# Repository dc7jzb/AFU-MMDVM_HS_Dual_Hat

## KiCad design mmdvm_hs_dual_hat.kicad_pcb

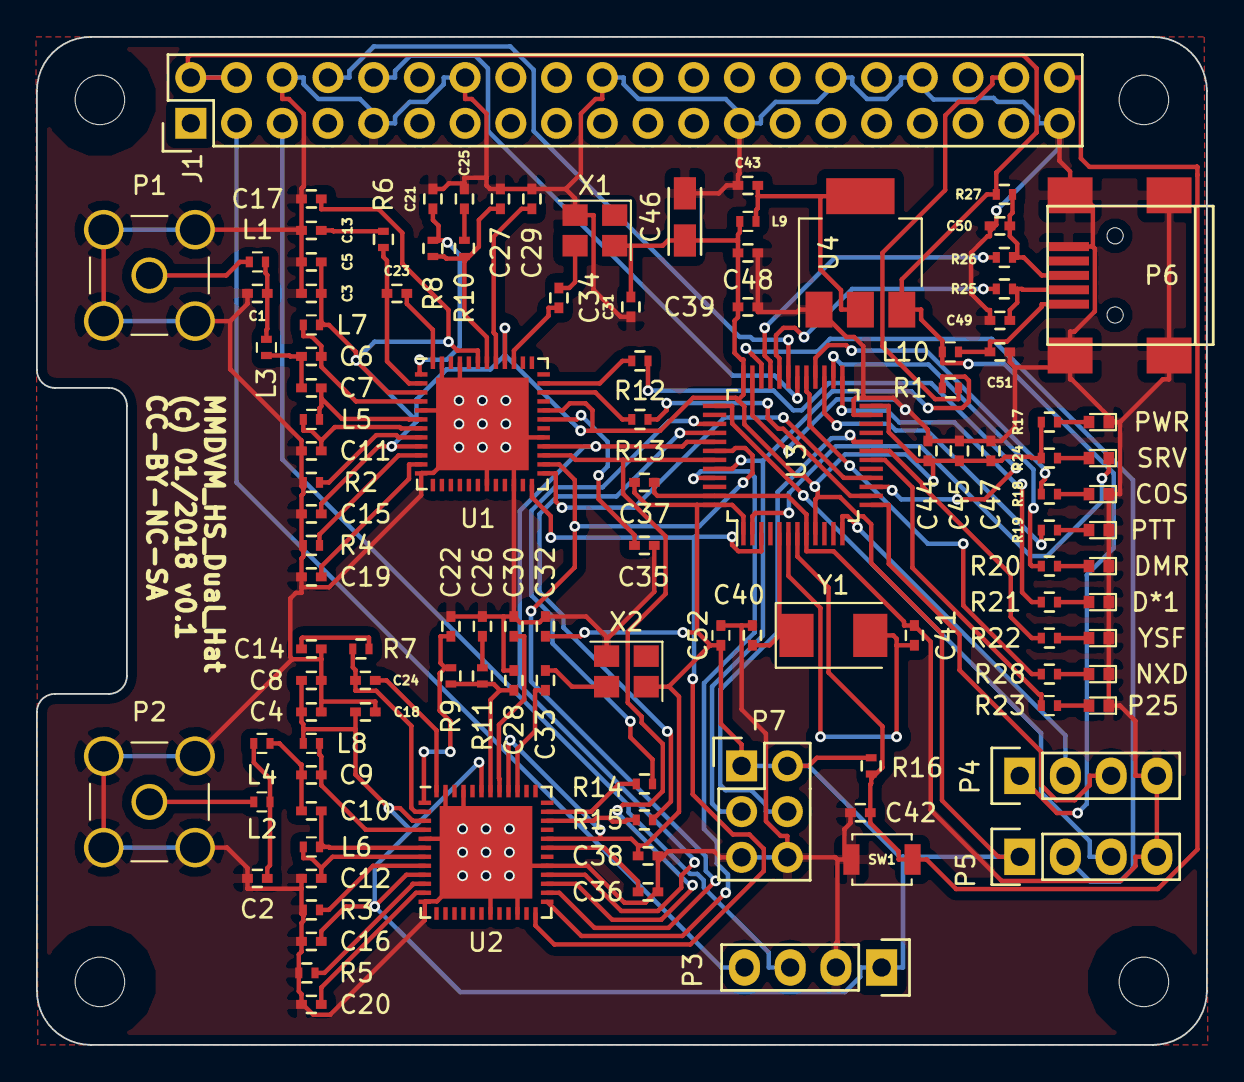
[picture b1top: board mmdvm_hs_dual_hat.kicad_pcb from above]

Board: 2 copper layers, 65.0 x 56.0 mm, 119 parts (0 on the bottom side), 92 nets.

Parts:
C1, C2, C11, C12: 6p8; C_0402
C3, C4, C15, C16, C17, C18, C31, C32, C37, C38, C39, C51, C52: 10n; C_0402
C5, C8: 220p; C_0402
C6, C9: 10p; C_0402
C7, C10: 4p7; C_0402
C13, C14, C19, C20, C29, C30, C35, C36, C42, C43, C44, C45, C47: 100n; C_0402
C21, C22: 470p; C_0402
C23, C24: 22n; C_0402
C25, C26: 15n; C_0402
C27, C28: 1n; C_0402
C33, C34: 22p; C_0402
C40, C41: 20p; C_0402
C46: 10u/10V; TantalC_SizeA_EIA-3216_Reflow
C48: 10u; C_0402
C49, C50: 47p; C_0402
COS: yellow; LED_0402
D*1: green; LED_0402
DMR: yellow; LED_0402
J1: RPi_GPIO; Pin_Header_Straight_2x20
L1, L2: 22n; L_0402
L3, L4: 20n; L_0402
L5, L6: 27n; L_0402
L7, L8: 13n; L_0402
L9: 10u; L_0402
L10: 100MHz; L_0402
NXD: blue; LED_0402
P1, P2: SMA; SMA_THT_Jack_Straight
P3: I2C; Pin_Header_Straight_1x04
P4: DISPLAY; Pin_Header_Straight_1x04
P5: STLINK; Pin_Header_Straight_1x04
P6: USB_OTG; USB_Mini-B
P7: CONN_02X03; Pin_Header_Straight_2x03
P25: red; LED_0402
PTT: red; LED_0402
PWR: green; LED_0402
R1, R16: 10k; R_0402
R2, R3: 1k1; R_0402
R4, R5: 3k8; R_0402
R6, R7: 3r9; R_0402
R8, R9: 560; R_0402
R10, R11: 270; R_0402
R12, R13, R14, R15, R17, R18, R19, R20, R21, R22, R23, R24, R28: 1k; R_0402
R25, R26: 27R; R_0402
R27: 1k5; R_0402
SRV: red; LED_0402
SW1: DNI; SW_SPST_B3U-1000P
U1, U2: ADF7021; QFN-48-1EP_7x7mm_Pitch0.5mm
U3: STM32F103C8T6; LQFP-48_7x7mm_Pitch0.5mm
U4: LD1117S33TR; SOT-223-3_TabPin2
X1: TCXO; Crystal_SMD_3225-4pin_3.2x2.5mm
X2: TCXO2; Crystal_SMD_3225-4pin_3.2x2.5mm
Y1: 8MHz; Crystal_SMD_Abracon_ABM3-2pin_5.0x3.2mm
YSF: amber; LED_0402
ol: RPi_Hat_Mounting_Hole
or: RPi_Hat_Mounting_Hole
ul: RPi_Hat_Mounting_Hole
ur: RPi_Hat_Mounting_Hole

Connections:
+3V3: C3.1, C4.1, C5.1, C8.1, C15.1, C16.1, C17.1, C18.1, C31.1, C32.1, C37.2, C38.2, C39.1, C44.1, C45.1, C46.1, C47.1, C48.1, C52.1, L7.2, L8.2, L9.2, P3.1, P5.1, P7.1, P7.2, R16.2, R17.2, R24.1, U1.3, U1.9, U1.32, U1.40, U1.43, U2.3, U2.9, U2.32, U2.40, U2.43, U3.1, U3.9, U3.24, U3.36, U3.48, X1.4, X2.4
+5V: J1.2, J1.4, L10.1, P4.1, R27.1, U4.3
BOOT0: P7.3, R1.1, U3.44
BOOT1: P7.4, U3.20
CE: U1.24, U2.24, U3.3
COS_LED: R18.2, U3.28
D+: R26.2, U3.33
D-: R25.2, U3.32
DATA1: R15.1, U3.40
DATA2: R13.1, U3.14
DCLK1: R14.1, U3.39
DCLK2: R12.1, U3.15
DISP_RXD: P4.3, U3.13
DISP_TXD: P4.2, U3.12
DMR_LED: R20.2, U3.26
DSTAR_LED: R21.2, U3.25
GND: C1.2, C2.2, C3.2, C4.2, C5.2, C8.2, C11.2, C12.2, C13.2, C14.2, C15.2, C16.2, C17.2, C18.2, C19.2, C20.2, C21.2, C22.2, C25.2, C26.2, C27.2, C28.2, C29.1, C30.1, C31.2, C32.2, C35.1, C36.1, C37.1, C38.1, C39.2, C40.2, C41.2, C42.2, C43.2, C44.2, C45.2, C46.2, C47.2, C48.2, C49.2, C50.1, C51.1, C52.2, COS.1, D*1.1, DMR.1, J1.6, J1.9, J1.14, J1.20, J1.25, J1.30, J1.34, J1.39, NXD.1, P1.2, P2.2, P3.2, P4.4, P5.4, P6.5, P6.6, P7.5, P7.6, P25.1, PTT.1, PWR.1, R2.2, R3.2, R4.2, R5.2, SW1.2, U1.5, U1.12, U1.19, U1.22, U1.29, U1.45, U1.47, U1.49, U2.5, U2.12, U2.19, U2.22, U2.29, U2.45, U2.47, U2.49, U3.8, U3.23, U3.35, U3.47, U4.1, X1.2, X2.2, YSF.1
NRST: C42.1, J1.40, R16.1, SW1.1, U3.7
NXDN_LED: R28.2, U3.29
unnamed: C1.1, L1.2, L3.1
unnamed: C2.1, L2.2, L4.1
unnamed: C6.1, L7.1, U1.4
unnamed: C6.2, C7.2, L3.2
unnamed: C7.1, L5.2, U1.6
unnamed: C9.1, L8.1, U2.4
unnamed: C10.1, L6.2, U2.6
unnamed: C9.2, C10.2, L4.2
unnamed: C11.1, L5.1, U1.7
unnamed: C12.1, L6.1, U2.7
unnamed: C13.1, R6.2
unnamed: C14.1, R7.2
unnamed: C19.1, U1.11
unnamed: C20.1, U2.11
unnamed: C21.1, R8.2, U1.1
unnamed: C22.1, R9.2, U2.1
unnamed: C23.1, U1.48
unnamed: C23.2, R6.1, U1.2
unnamed: C24.1, U2.48
unnamed: C24.2, R7.1, U2.2
unnamed: C25.1, R10.2
unnamed: C26.1, R11.2
unnamed: C27.1, R8.1, R10.1, U1.42
unnamed: C28.1, R9.1, R11.1, U2.42
unnamed: C29.2, U1.41
unnamed: C30.2, U2.41
unnamed: C33.1, U2.39
unnamed: C34.2, U1.39
unnamed: C35.2, U1.31
unnamed: C36.2, U2.31
unnamed: C40.1, U3.5, Y1.1
unnamed: C41.1, U3.6, Y1.2
unnamed: C43.1, L9.1, U4.2
unnamed: C49.1, P6.2, R25.1
unnamed: C50.2, P6.3, R26.1, R27.2
unnamed: C51.2, L10.2, P6.1
unnamed: COS.2, R18.1
unnamed: D*1.2, R21.1
unnamed: DMR.2, R20.1
unnamed: J1.38, R1.2
unnamed: L1.1, P1.1
unnamed: L2.1, P2.1
unnamed: NXD.2, R28.1
unnamed: P25.2, R23.1
unnamed: PTT.2, R19.1
unnamed: PWR.2, R17.1
unnamed: R2.1, U1.8
unnamed: R3.1, U2.8
unnamed: R4.1, U1.10
unnamed: R5.1, U2.10
unnamed: R12.2, U1.35
unnamed: R13.2, U1.34
unnamed: R14.2, U2.35
unnamed: R15.2, U2.34
unnamed: R22.1, YSF.2
unnamed: R24.2, SRV.2
P25_LED: R23.2, U3.18
PTT_LED: R19.2, U3.27
RXD: J1.8, U3.31
SCL: J1.5, P3.3
SCLK: U1.28, U2.28, U3.41
SDA: J1.3, P3.4
SDATA: U1.26, U2.26, U3.42
SERVICE: SRV.1, U3.2
SLE1: U2.25, U3.45
SLE2: U1.25, U3.16
SREAD: U1.27, U2.27, U3.43
SWCLK: P5.3, U3.37
SWDIO: P5.2, U3.34
TCXO: C34.1, X1.3
TCXO2: C33.2, X2.3
TXD: J1.10, U3.30
YSF_LED: R22.2, U3.19

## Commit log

2018-02-02 add holes and more GND on PCB
2018-02-02 Stencil added
2018-02-02 seed files added

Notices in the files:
mmdvm_hs_dual_hat.kicad_pcb:
CC-BY-NC-SA
